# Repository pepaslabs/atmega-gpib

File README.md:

# atmega-gpib
An ATmega-based GPIB-to-USB adapter board.

# Status

This board is untested.

# Board design v1

Initial board design.

## Gerbers

[gerbers.zip](kicad/releases/v1/gerbers.zip)

## Schematic

[PDF](kicad/releases/v1/atmega-gpib-schematic.pdf).

# License

This board design is [Open-Source Hardware](http://www.oshwa.org/definition/).  It is licensed under the [MIT License](http://opensource.org/licenses/MIT).  It was designed by Jason Pepas.

# Thanks

Thanks to [Steven Casagrande](http://steven.casagrande.io/) of [Galvant Industries](https://github.com/Galvant) for [releasing](https://github.com/Galvant/gpibusb-pcb) his [GPIB-to-USB adapter](http://www.galvant.ca/) as open source hardware.  Using a few of his KiCAD footprints saved me a lot of time!

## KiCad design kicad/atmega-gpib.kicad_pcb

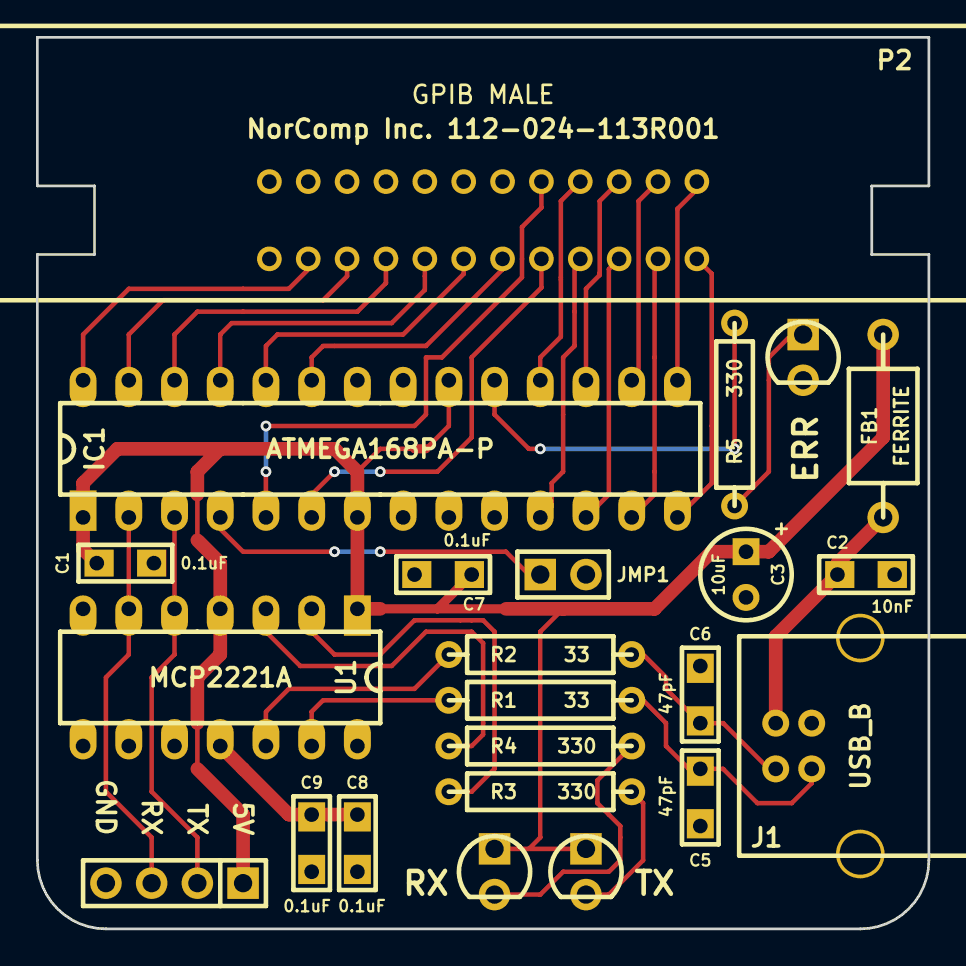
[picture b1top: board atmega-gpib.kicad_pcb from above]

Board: 2 copper layers, 49.5 x 49.5 mm, 23 parts (0 on the bottom side), 33 nets.

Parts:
C1, C7, C8, C9: 0.1uF; CERCAP_15_059B_0805
C2: 10nF; CERCAP_15_059B_0805
C3: 10uF; ELCAP_10_20_V_059A
C5, C6: 47pF; CERCAP_15_059B_0805
D1: TX; LED_3MM_069A
D2: RX; LED_3MM_069A
D3: ERR; LED_3MM_069A
FB1: FERRITE; FERRITE_AXIAL_04_069A
IC1: ATMEGA168PA-P; DIP28_PL
J1: USB_B
JMP1: CONN_2X1; SIL-2
P1: CONN_4X1; SIL-4
P2: GPIB; 112-024-113R001
R1, R2: 33; R_AXIAL_0W25_059A_PL
R3, R4, R5: 330; R_AXIAL_0W25_059A_PL
U1: MCP2221A; DIP14_PL

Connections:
5V: C1.1, C3.1, C7.1, D1.1, D2.1, FB1.2, IC1.1, IC1.7, IC1.20, P1.1, U1.1, U1.4
ERR_LED: IC1.19, R5.2
GND: C1.2, C2.2, C3.2, C5.2, C6.2, C7.2, C8.2, C9.2, D3.2, IC1.8, IC1.22, J1.4, J1.5, J1.6, JMP1.2, P1.4, P2.12, P2.18, P2.19, P2.20, P2.21, P2.22, P2.23, P2.24, U1.14
JMP1: IC1.4, JMP1.1
unnamed: IC1.28, P2.11
unnamed: IC1.25, P2.8
unnamed: IC1.6, P2.5
unnamed: IC1.23, P2.6
unnamed: IC1.24, P2.7
unnamed: IC1.26, P2.9
unnamed: IC1.27, P2.10
unnamed: R4.1, U1.3
unnamed: D2.2, R4.2
unnamed: C8.1, C9.1, U1.11
unnamed: R1.1, U1.13
unnamed: R3.1, U1.2
unnamed: IC1.18, P2.16
unnamed: IC1.11, P2.4
unnamed: IC1.15, P2.13
unnamed: IC1.16, P2.14
unnamed: IC1.17, P2.15
unnamed: IC1.5, P2.17
unnamed: D3.1, R5.1
unnamed: IC1.13, P2.2
unnamed: IC1.12, P2.3
unnamed: C5.1, J1.3, R1.2
unnamed: D1.2, R3.2
unnamed: IC1.14, P2.1
unnamed: R2.1, U1.12
unnamed: C6.1, J1.2, R2.2
unnamed: C2.1, FB1.1, J1.1
RX: IC1.2, P1.3, U1.6
TX: IC1.3, P1.2, U1.5

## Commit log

2017-05-08 initial release
2017-05-08 adding schematic
2017-05-20 rotating pdf
2017-06-01 adding clean script
2017-06-01 migrating board back to kicad 'old stable'
2017-06-01 cleaning out old lib
2017-06-01 pulling in updated parts
2017-06-01 interim schematic update commit
2017-07-04 hello-world firmware
2017-07-04 working on firmware
2017-07-04 firmware still not working
2017-08-27 changing controller address
2017-08-28 pulling in HP docs on GPIB
2017-09-02 very basic working read and write to Keithley 196
2017-09-02 Adding support for v1 and v2 boards
2017-09-02 adding ++baud command
2017-09-03 Working on board v2
2017-09-03 v2 board
2017-09-03 Fixing drill file offset
2017-09-03 Fixing drill offsets again
2017-09-03 adding board renders
2017-09-03 refactoring commands to be more data-like
2017-09-05 adding some scripts
2017-09-05 working on making a non-blocking main loop
2017-09-07 updating changelog
